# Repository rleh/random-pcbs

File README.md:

# Random PCBs

Some devboards I happed to design and wanted to share...

## License

This work is licensed under a [Creative Commons Attribution-ShareAlike 4.0 International License](https://creativecommons.org/licenses/by-sa/4.0/).

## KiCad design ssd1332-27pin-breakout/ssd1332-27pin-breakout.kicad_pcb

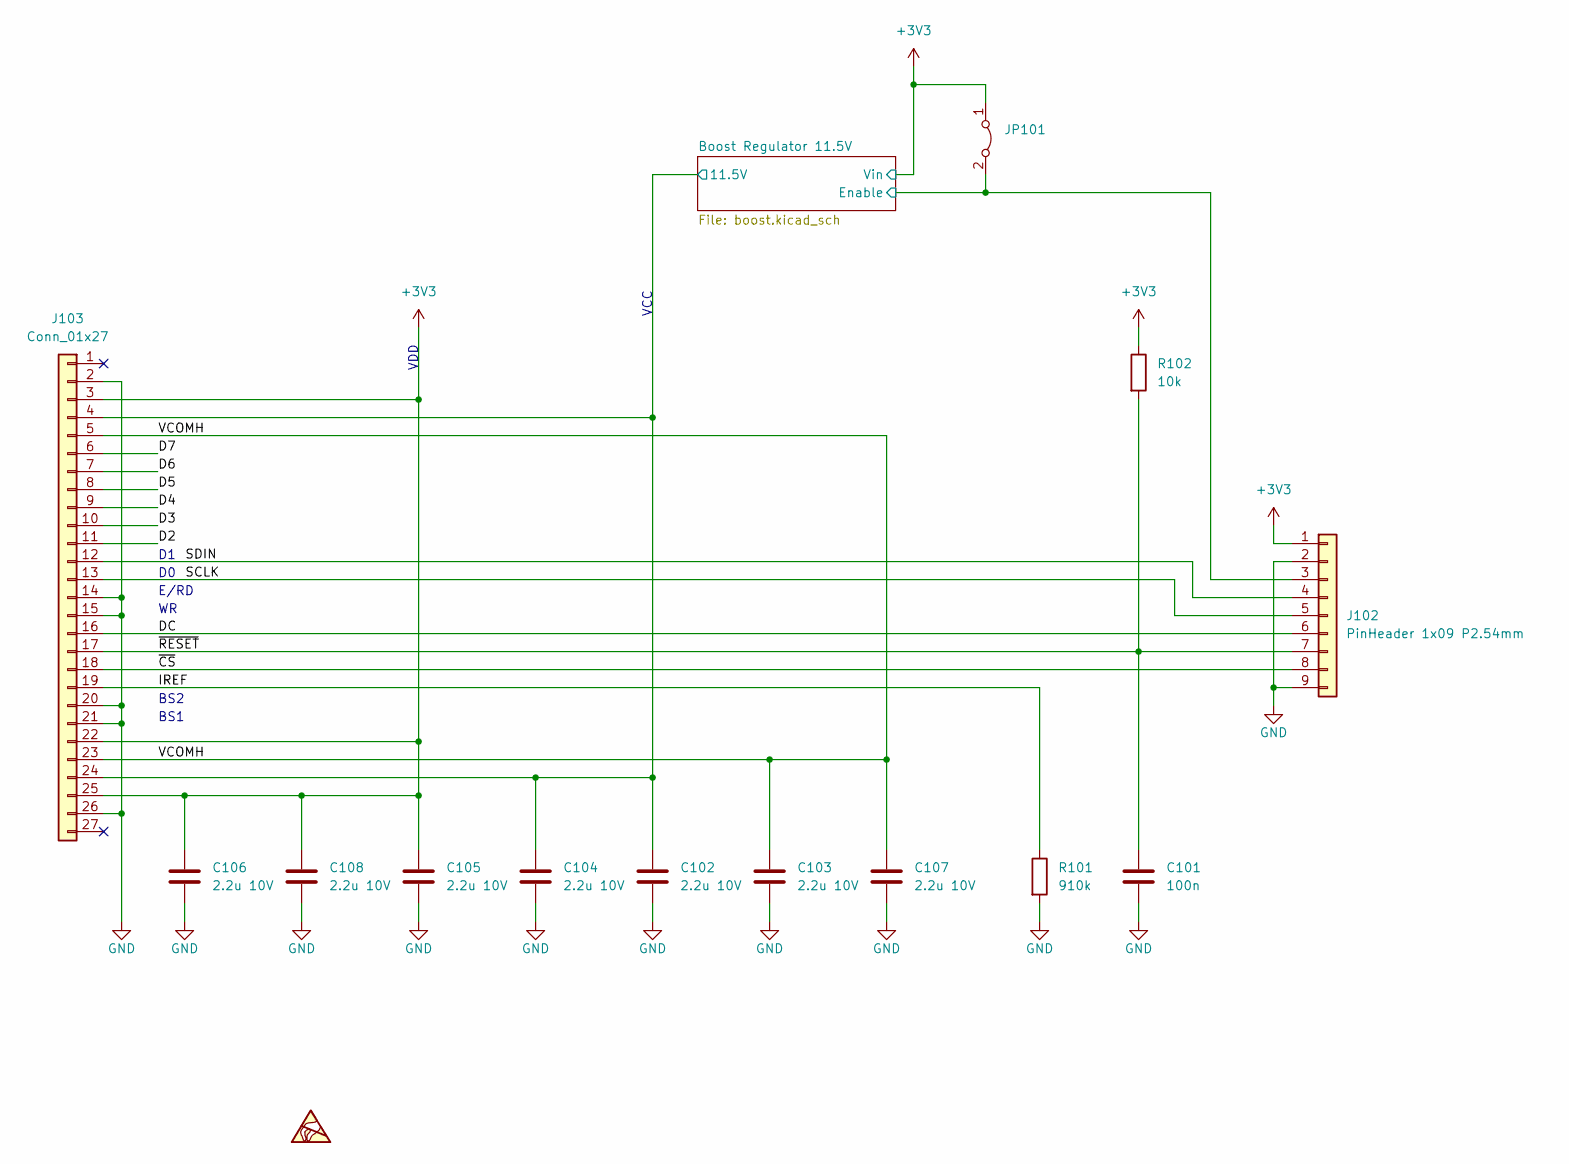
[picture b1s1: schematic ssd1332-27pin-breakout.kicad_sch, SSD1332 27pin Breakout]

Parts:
C101: 100n; C_0603_1608Metric
C102, C103, C104, C105, C106, C107, C108: 2.2u 10V; C_0603_1608Metric
J102: PinHeader 1x09 P2.54mm; PinHeader_1x09_P2.54mm_Vertical
J103: Conn_01x27; Display_27pin_P0.8_DirectSoldering
JP101: SolderJumper-2_P1.3mm_Bridged_RoundedPad1.0x1.5mm
R101: 910k; R_0603_1608Metric
R102: 10k; R_0603_1608Metric
SYM101: ESD-Logo_6.6x6mm_SilkScreen

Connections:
+3V3: C105.1, C106.1, C108.1, J102.1, J103.3, J103.22, J103.25, JP101.1 (A), R102.1; also elsewhere on the board
/Boost Regulator 11.5V/11.5V: C102.1, C104.1, J103.4, J103.24; also elsewhere on the board
/Boost Regulator 11.5V/Enable: J102.3, JP101.2 (B); also elsewhere on the board
/D2: J103.11
/D3: J103.10
/D4: J103.9
/D5: J103.8
/D6: J103.7
/D7: J103.6
/DC: J102.6, J103.16
/IREF: J103.19, R101.1
/SCLK: J102.5, J103.13
/SDIN: J102.4, J103.12
/VCOMH: C103.1, C107.1, J103.5, J103.23
/~CS: J102.8, J103.18
/~RESET: C101.1, J102.7, J103.17, R102.2
GND: C101.2, C102.2, C103.2, C104.2, C105.2, C106.2, C107.2, C108.2, J102.2, J102.9, J103.2, J103.14, J103.15, J103.20, J103.21, J103.26, R101.2; also elsewhere on the board

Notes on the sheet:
VCC
BS2
BS1
E/RD
VDD

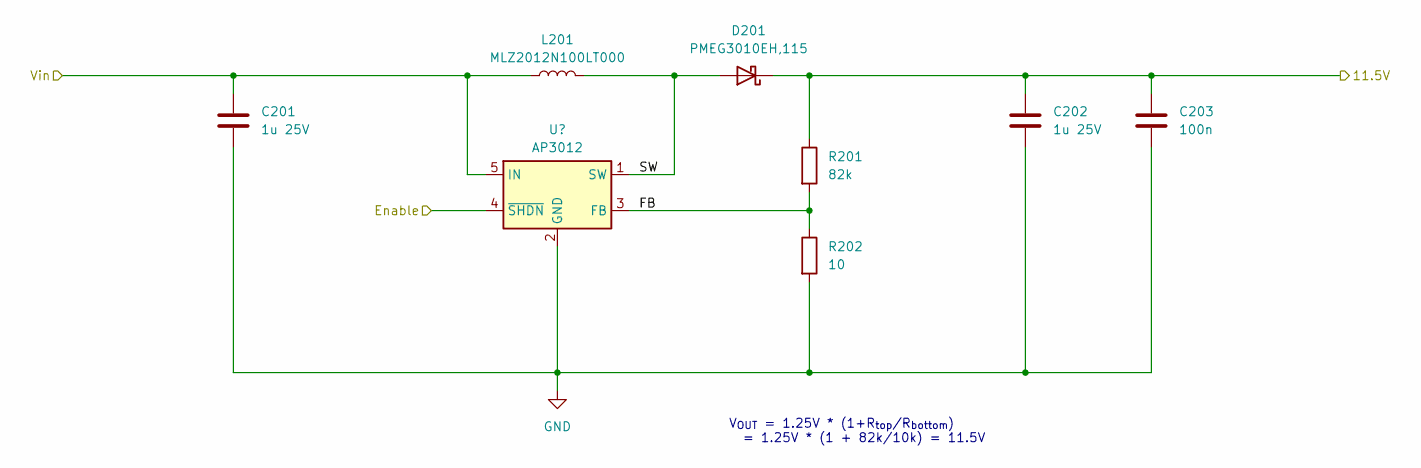
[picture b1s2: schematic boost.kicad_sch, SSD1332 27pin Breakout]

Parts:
C201, C202: 1u 25V; C_0603_1608Metric
C203: 100n; C_0603_1608Metric
D201: PMEG3010EH,115; D_SOD-123F
L201: MLZ2012N100LT000; L_0805_2012Metric
R201: 82k; R_0603_1608Metric
R202: 10; R_0603_1608Metric
U201: AP3012; SOT-23-5

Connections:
+3V3: C201.1, L201.1, U201.5 (IN); also elsewhere on the board
/Boost Regulator 11.5V/11.5V: C202.1, C203.1, D201.1 (K), R201.1; also elsewhere on the board
/Boost Regulator 11.5V/Enable: U201.4 (~SHDN); also elsewhere on the board
/Boost Regulator 11.5V/FB: R201.2, R202.1, U201.3 (FB)
/Boost Regulator 11.5V/SW: D201.2 (A), L201.2, U201.1 (SW)
GND: C201.2, C202.2, C203.2, R202.2, U201.2 (GND); also elsewhere on the board

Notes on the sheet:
V_{OUT} = 1.25V * (1+R_{top}/R_{bottom}) = 1.25V * (1 + 82k/10k) = 11.5V

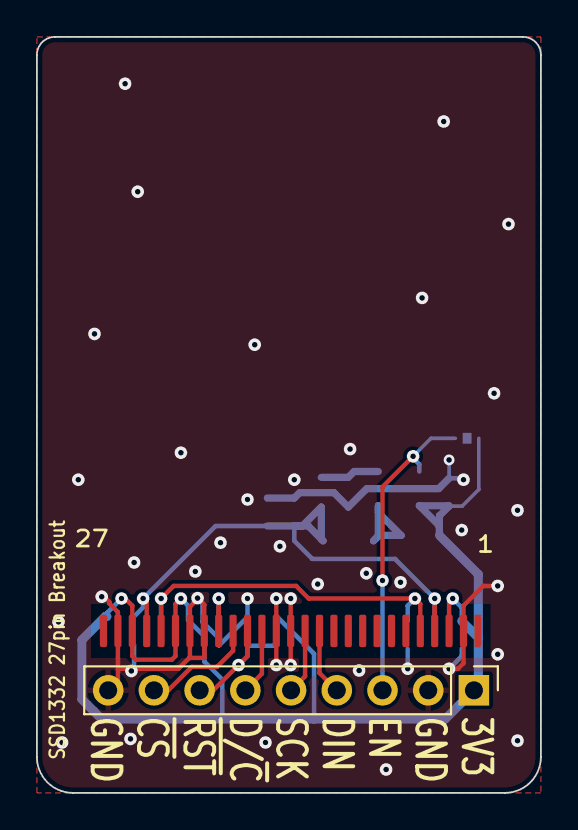
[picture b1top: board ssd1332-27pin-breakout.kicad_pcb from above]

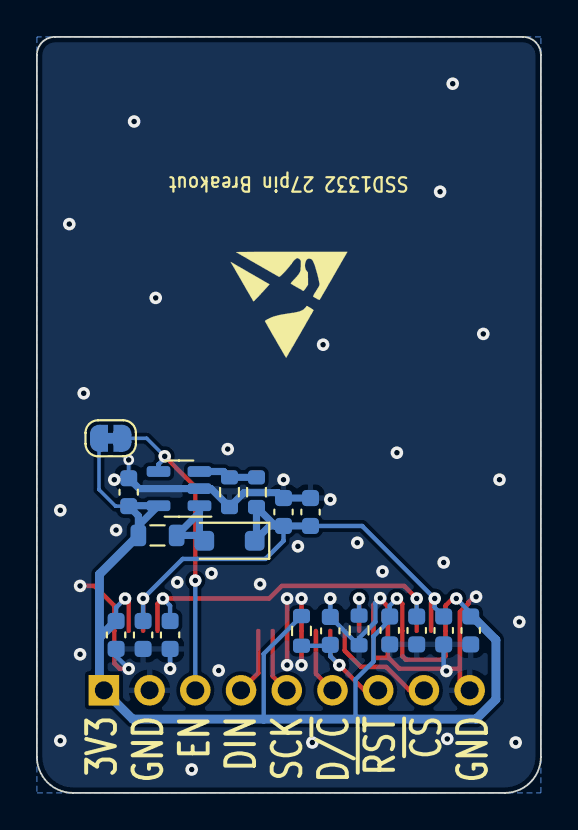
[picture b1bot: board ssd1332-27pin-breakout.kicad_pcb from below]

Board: 2 copper layers, 28.0 x 42.0 mm, 22 parts (20 on the bottom side), 13 nets.

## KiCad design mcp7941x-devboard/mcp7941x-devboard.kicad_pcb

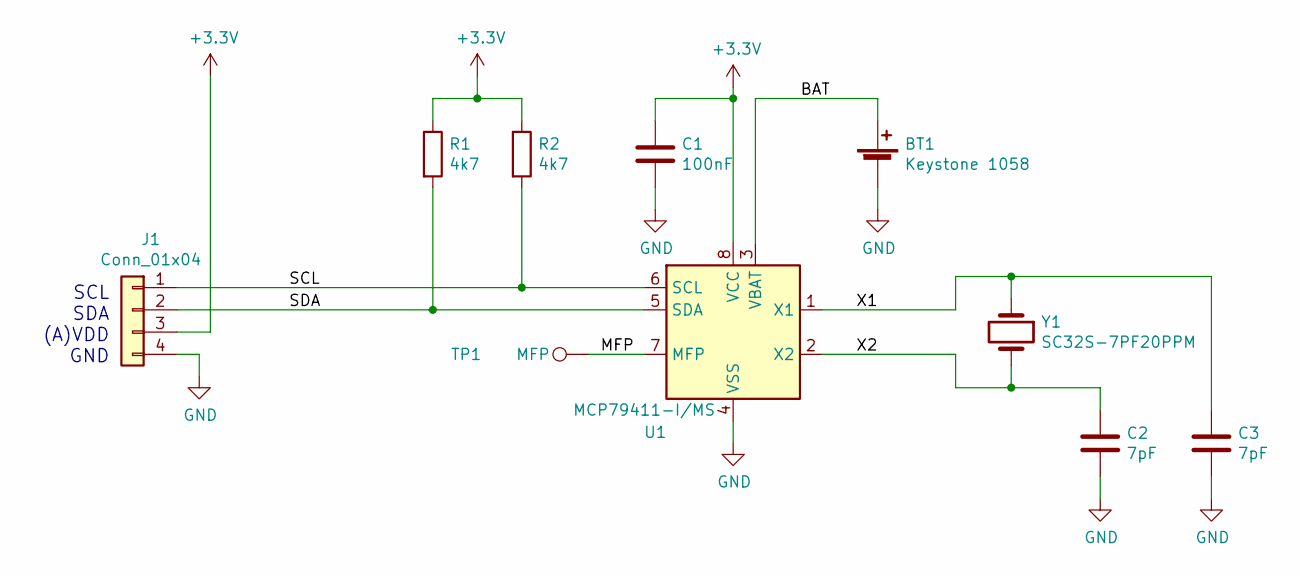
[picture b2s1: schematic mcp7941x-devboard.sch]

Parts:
BT1: Keystone 1058; BatteryHolder_Keystone_1058_1x2032
C1: 100nF; C_0603_1608Metric
C2, C3: 7pF; C_0603_1608Metric
J1: Conn_01x04; PinHeader_1x04_P2.54mm_Vertical
R1, R2: 4k7; R_0603_1608Metric
TP1: MFP; TestPoint_THTPad_D1.5mm_Drill0.7mm
U1: MCP79411-I/MS; MSOP-8_3x3mm_P0.65mm
Y1: SC32S-7PF20PPM; Crystal_SMD_3215-2Pin_3.2x1.5mm

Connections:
+3V3: C1.1, J1.3, R1.1, R2.1, U1.8 (VCC)
/BAT: BT1.1 (+), U1.3 (VBAT)
/MFP: TP1.1, U1.7 (MFP)
/SCL: J1.1, R2.2, U1.6 (SCL)
/SDA: J1.2, R1.2, U1.5 (SDA)
/X1: C3.1, U1.1 (X1), Y1.1
/X2: C2.1, U1.2 (X2), Y1.2
GND: BT1.2 (-), C1.2, C2.2, C3.2, J1.4, U1.4 (VSS)

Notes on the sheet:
SCL SDA (A)VDD GND

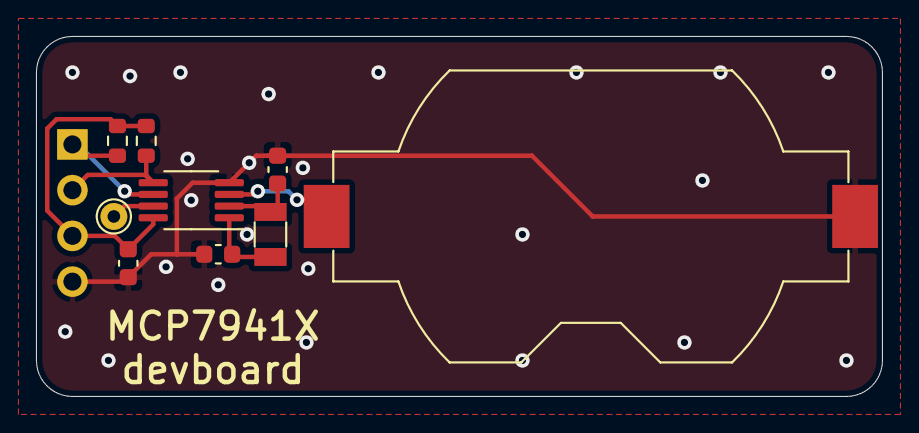
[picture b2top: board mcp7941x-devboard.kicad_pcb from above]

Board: 2 copper layers, 47.0 x 20.0 mm, 10 parts (1 on the bottom side), 8 nets.

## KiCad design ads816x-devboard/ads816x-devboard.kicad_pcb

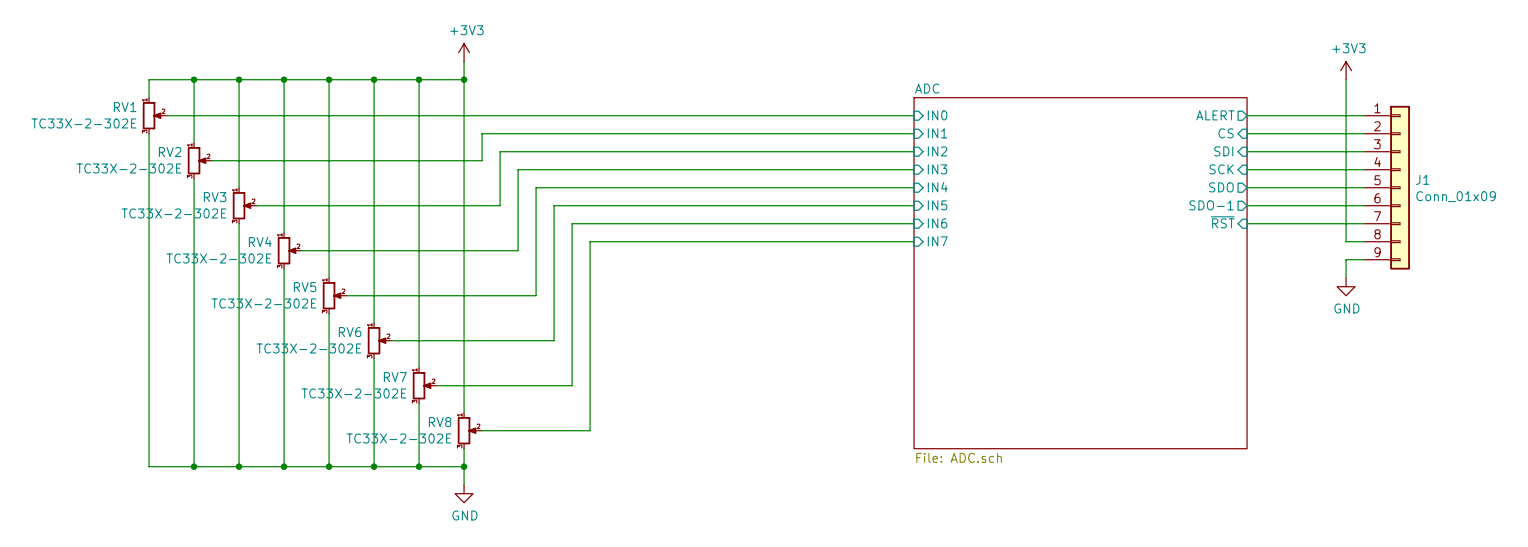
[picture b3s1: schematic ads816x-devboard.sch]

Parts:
J1: Conn_01x09; PinHeader_1x09_P2.54mm_Vertical
RV1, RV2, RV3, RV4, RV5, RV6, RV7, RV8: TC33X-2-302E; Potentiometer_Bourns_TC33X_Vertical

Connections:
+3V3: J1.8, RV1.1, RV2.1, RV3.1, RV4.1, RV5.1, RV6.1, RV7.1, RV8.1; also elsewhere on the board
/ADC/ALERT: J1.1; also elsewhere on the board
/ADC/CS: J1.2; also elsewhere on the board
/ADC/IN0: RV1.2; also elsewhere on the board
/ADC/IN1: RV2.2; also elsewhere on the board
/ADC/IN2: RV3.2; also elsewhere on the board
/ADC/IN3: RV4.2; also elsewhere on the board
/ADC/IN4: RV5.2; also elsewhere on the board
/ADC/IN5: RV6.2; also elsewhere on the board
/ADC/IN6: RV7.2; also elsewhere on the board
/ADC/IN7: RV8.2; also elsewhere on the board
/ADC/SCK: J1.4; also elsewhere on the board
/ADC/SDI: J1.3; also elsewhere on the board
/ADC/SDO: J1.5; also elsewhere on the board
/ADC/SDO-1: J1.6; also elsewhere on the board
/ADC/~RST: J1.7; also elsewhere on the board
GND: J1.9, RV1.3, RV2.3, RV3.3, RV4.3, RV5.3, RV6.3, RV7.3, RV8.3; also elsewhere on the board

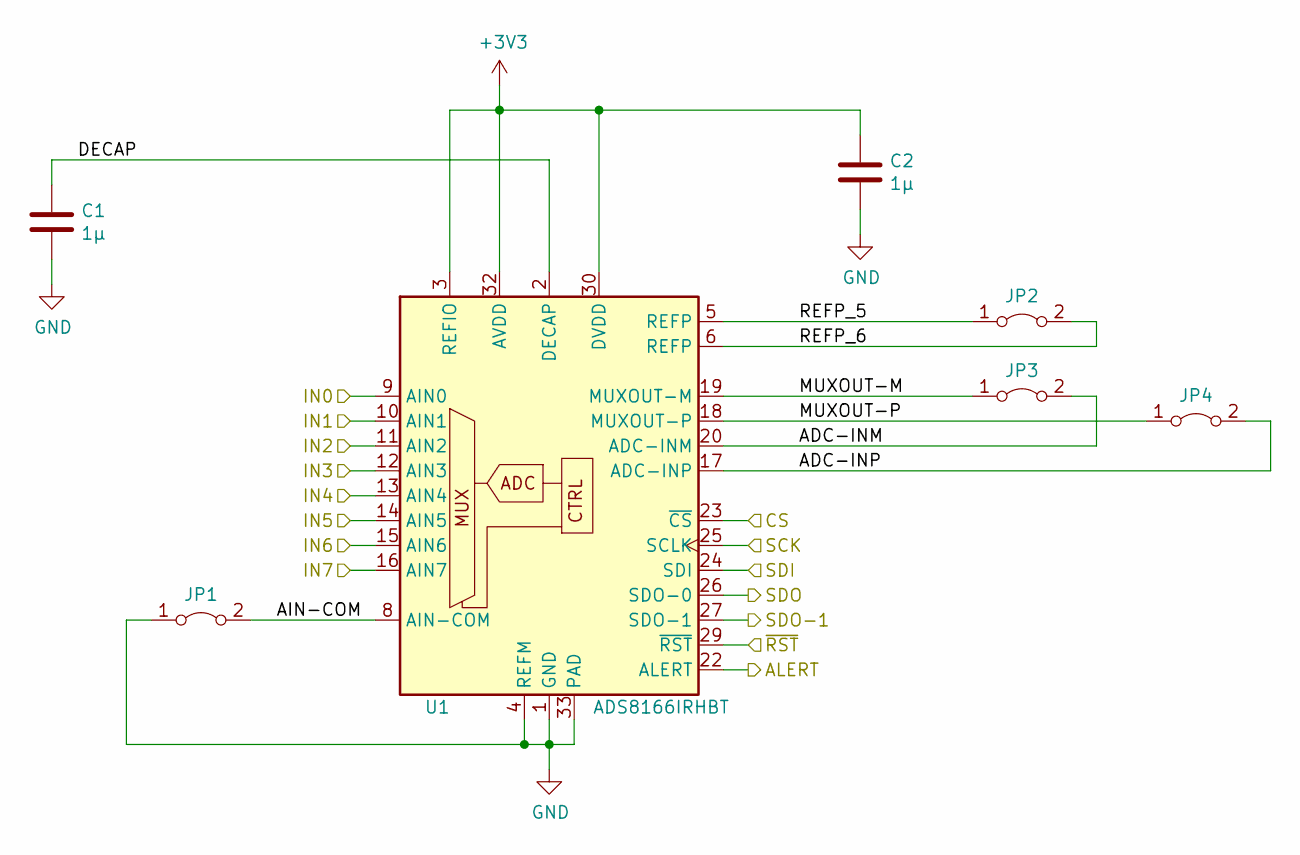
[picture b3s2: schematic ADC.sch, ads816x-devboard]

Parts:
C1, C2: 1µ; C_0603_1608Metric
JP1, JP2, JP3, JP4: Jumper_2_Bridged; SolderJumper-2_P1.3mm_Bridged_RoundedPad1.0x1.5mm
U1: ADS8166IRHBT; VQFN-32-1EP_5x5mm_P0.5mm_EP3.1x3.1mm

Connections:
+3V3: C2.1, U1.3 (REFIO), U1.30 (DVDD), U1.32 (AVDD); also elsewhere on the board
/ADC/ADC-INM: JP3.2 (B), U1.20 (ADC-INM)
/ADC/ADC-INP: JP4.2 (B), U1.17 (ADC-INP)
/ADC/AIN-COM: JP1.2 (B), U1.8 (AIN-COM)
/ADC/ALERT: U1.22 (ALERT); also elsewhere on the board
/ADC/CS: U1.23 (~CS); also elsewhere on the board
/ADC/DECAP: C1.1, U1.2 (DECAP)
/ADC/IN0: U1.9 (AIN0); also elsewhere on the board
/ADC/IN1: U1.10 (AIN1); also elsewhere on the board
/ADC/IN2: U1.11 (AIN2); also elsewhere on the board
/ADC/IN3: U1.12 (AIN3); also elsewhere on the board
/ADC/IN4: U1.13 (AIN4); also elsewhere on the board
/ADC/IN5: U1.14 (AIN5); also elsewhere on the board
/ADC/IN6: U1.15 (AIN6); also elsewhere on the board
/ADC/IN7: U1.16 (AIN7); also elsewhere on the board
/ADC/MUXOUT-M: JP3.1 (A), U1.19 (MUXOUT-M)
/ADC/MUXOUT-P: JP4.1 (A), U1.18 (MUXOUT-P)
/ADC/REFP_5: JP2.1 (A), U1.5 (REFP)
/ADC/REFP_6: JP2.2 (B), U1.6 (REFP)
/ADC/SCK: U1.25 (SCLK); also elsewhere on the board
/ADC/SDI: U1.24 (SDI); also elsewhere on the board
/ADC/SDO: U1.26 (SDO-0); also elsewhere on the board
/ADC/SDO-1: U1.27 (SDO-1); also elsewhere on the board
/ADC/~RST: U1.29 (~RST); also elsewhere on the board
GND: C1.2, C2.2, JP1.1 (A), U1.1 (GND), U1.4 (REFM), U1.21 (GND), U1.31 (GND), U1.33 (PAD); also elsewhere on the board

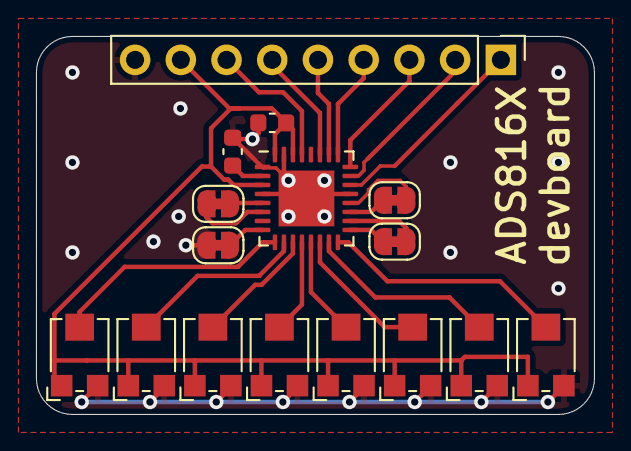
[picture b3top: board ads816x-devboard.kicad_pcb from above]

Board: 2 copper layers, 31.0 x 21.0 mm, 16 parts (0 on the bottom side), 25 nets.

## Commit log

2021-12-23 Add ADS816x devboard
2021-12-23 Add MCP7941x devboard
2023-11-14 Add SSD1332 27-pin P0.8mm Breakout with integrated DC/DC Boost
2023-11-14 Gerber files for ssd1332-27pin-breakout
2025-02-16 iBOM HTML export for ssd1332-27pin-breakout

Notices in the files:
ads816x-devboard/ADC.sch:
License: CC BY-SA 4.0
